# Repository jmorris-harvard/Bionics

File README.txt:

NanoDesign x Bionics Collab File Storage

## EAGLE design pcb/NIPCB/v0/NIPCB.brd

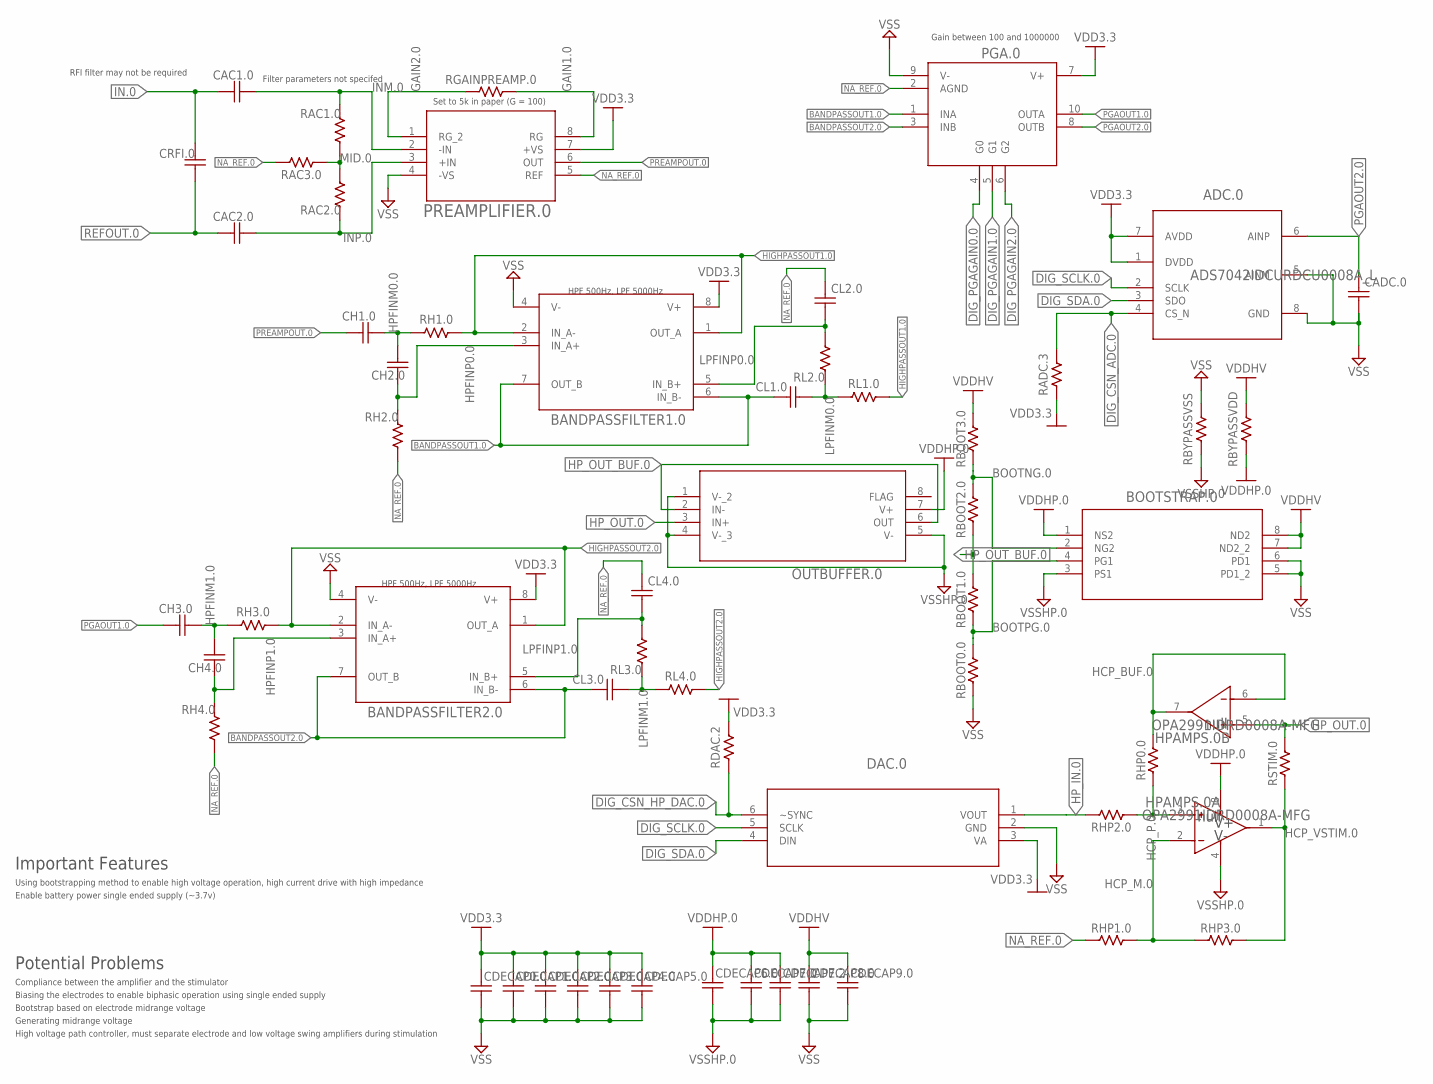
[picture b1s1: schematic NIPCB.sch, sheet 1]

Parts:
ADC.0: ADS7042IDCURDCU0008A_L; DCU0008A_L
BANDPASSFILTER1.0, BANDPASSFILTER2.0: OPA2325IDRD8_TEX; D8_TEX
BOOTSTRAP.0: DMC4047LSD-13SO8_DIO; SO8_DIO
CAC1.0, CAC2.0: C-US0402; 0402
CADC.0: C-US0402; 0402
CDECAP0.0, CDECAP1.0, CDECAP2.0, CDECAP3.0, CDECAP4.0, CDECAP5.0, CDECAP6.0, CDECAP7.0, CDECAP7.2, CDECAP8.0, CDECAP9.0: C-US0402; 0402
CH1.0, CH2.0, CH3.0, CH4.0: C-US0402; 0402
CL1.0, CL2.0, CL3.0, CL4.0: C-US0402; 0402
CRFI.0: C-US0402; 0402
DAC.0: DAC081S101CIMKX/NOPBMK06A; MK06A
HPAMPS.0: OPA2991IDRD0008A-MFG; D0008A-MFG
OUTBUFFER.0: OPA552UA/2K5D8; D8
PGA.0: LTC6911CMS-1TRPBFMSOP-10_MS_LIT; MSOP-10_MS_LIT
PREAMPLIFIER.0: INA818IDSOIC-8_TEX; SOIC-8_TEX
RAC1.0, RAC2.0, RAC3.0: R-US0402; 0402
RADC.3: R-US0402; 0402
RBOOT0.0, RBOOT1.0, RBOOT2.0, RBOOT3.0: R-US0603; 0603
RBYPASSVDD: R-US0402; 0402
RBYPASSVSS: R-US0402; 0402
RDAC.2: R-US0402; 0402
RGAINPREAMP.0: R-US0402; 0402
RH1.0, RH2.0, RH3.0, RH4.0: R-US0402; 0402
RHP0.0, RHP1.0, RHP2.0, RHP3.0: R-US0603; 0603
RL1.0, RL2.0, RL3.0, RL4.0: R-US0402; 0402
RSTIM.0: R-US0603; 0603

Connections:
BANDPASSOUT1.0: BANDPASSFILTER1.0.6 (IN_B-), BANDPASSFILTER1.0.7 (OUT_B), CL1.0.1, PGA.0.1 (INA)
BANDPASSOUT2.0: BANDPASSFILTER2.0.6 (IN_B-), BANDPASSFILTER2.0.7 (OUT_B), CL3.0.1, PGA.0.3 (INB)
BOOTNG.0: BOOTSTRAP.0.2 (NG2), RBOOT2.0.2, RBOOT3.0.1
BOOTPG.0: BOOTSTRAP.0.4 (PG1), RBOOT0.0.2, RBOOT1.0.1
DIG_CSN_ADC.0: ADC.0.4 (CS_N), RADC.3.1; also elsewhere on the board
DIG_CSN_HP_DAC.0: DAC.0.6 (~SYNC), RDAC.2.2; also elsewhere on the board
DIG_PGAGAIN0.0: PGA.0.4 (G0); also elsewhere on the board
DIG_PGAGAIN1.0: PGA.0.5 (G1); also elsewhere on the board
DIG_PGAGAIN2.0: PGA.0.6 (G2); also elsewhere on the board
DIG_SCLK.0: ADC.0.2 (SCLK), DAC.0.5 (SCLK); also elsewhere on the board
DIG_SDA.0: ADC.0.3 (SDO), DAC.0.4 (DIN); also elsewhere on the board
GAIN1.0: PREAMPLIFIER.0.8 (RG), RGAINPREAMP.0.1
GAIN2.0: PREAMPLIFIER.0.1 (RG_2), RGAINPREAMP.0.2
HCP_BUF.0: HPAMPS.0.6 (IN2-), HPAMPS.0.7 (OUT2), RHP0.0.2
HCP_M.0: HPAMPS.0.2 (IN1-), RHP1.0.2, RHP3.0.1
HCP_P.0: HPAMPS.0.3 (IN1+), RHP0.0.1, RHP2.0.1
HCP_VSTIM.0: HPAMPS.0.1 (OUT1), RHP3.0.2, RSTIM.0.1
HIGHPASSOUT1.0: BANDPASSFILTER1.0.1 (OUT_A), BANDPASSFILTER1.0.2 (IN_A-), RH1.0.1, RL1.0.1
HIGHPASSOUT2.0: BANDPASSFILTER2.0.1 (OUT_A), BANDPASSFILTER2.0.2 (IN_A-), RH3.0.1, RL4.0.1
HPFINM0.0: CH1.0.2, CH2.0.2, RH1.0.2
HPFINM1.0: CH3.0.2, CH4.0.2, RH3.0.2
HPFINP0.0: BANDPASSFILTER1.0.3 (IN_A+), CH2.0.1, RH2.0.1
HPFINP1.0: BANDPASSFILTER2.0.3 (IN_A+), CH4.0.1, RH4.0.1
HP_IN.0: DAC.0.1 (VOUT), RHP2.0.2
HP_OUT.0: HPAMPS.0.5 (IN2+), OUTBUFFER.0.3 (IN+), RSTIM.0.2; also elsewhere on the board
HP_OUT_BUF.0: OUTBUFFER.0.2 (IN-), OUTBUFFER.0.6 (OUT), RBOOT1.0.2, RBOOT2.0.1
IN.0: CAC1.0.1, CRFI.0.2; also elsewhere on the board
INM.0: CAC1.0.2, PREAMPLIFIER.0.2 (-IN), RAC1.0.2
INP.0: CAC2.0.2, PREAMPLIFIER.0.3 (+IN), RAC2.0.1
LPFINM0.0: CL1.0.2, RL1.0.2, RL2.0.1
LPFINM1.0: CL3.0.2, RL3.0.1, RL4.0.2
LPFINP0.0: BANDPASSFILTER1.0.5 (IN_B+), CL2.0.1, RL2.0.2
LPFINP1.0: BANDPASSFILTER2.0.5 (IN_B+), CL4.0.1, RL3.0.2
MID.0: RAC1.0.1, RAC2.0.2, RAC3.0.1
NA_REF.0: CL2.0.2, CL4.0.2, PGA.0.2 (AGND), PREAMPLIFIER.0.5 (REF), RAC3.0.2, RH2.0.2, RH4.0.2, RHP1.0.1; also elsewhere on the board
PGAOUT1.0: CH3.0.1, PGA.0.10 (OUTA)
PGAOUT2.0: ADC.0.6 (AINP), CADC.0.2, PGA.0.8 (OUTB)
PREAMPOUT.0: CH1.0.1, PREAMPLIFIER.0.6 (OUT)
REFOUT.0: CAC2.0.1, CRFI.0.1; also elsewhere on the board
VDD3.3: ADC.0.1 (DVDD), ADC.0.7 (AVDD), BANDPASSFILTER1.0.8 (V+), BANDPASSFILTER2.0.8 (V+), CDECAP0.0.1, CDECAP1.0.1, CDECAP2.0.1, CDECAP3.0.1, CDECAP4.0.1, CDECAP5.0.1, DAC.0.3 (VA), PGA.0.7 (V+), PREAMPLIFIER.0.7 (+VS), RADC.3.2, RDAC.2.1; also elsewhere on the board
VDDHP.0: BOOTSTRAP.0.1 (NS2), CDECAP6.0.1, CDECAP7.0.1, CDECAP7.2.1, HPAMPS.0.8 (V+), OUTBUFFER.0.7 (V+), RBYPASSVDD.2
VDDHV: BOOTSTRAP.0.7 (ND2_2), BOOTSTRAP.0.8 (ND2), CDECAP8.0.1, CDECAP9.0.1, RBOOT3.0.2, RBYPASSVDD.1; also elsewhere on the board
VSS: ADC.0.5 (AINM), ADC.0.8 (GND), BANDPASSFILTER1.0.4 (V-), BANDPASSFILTER2.0.4 (V-), BOOTSTRAP.0.5 (PD1_2), BOOTSTRAP.0.6 (PD1), CADC.0.1, CDECAP0.0.2, CDECAP1.0.2, CDECAP2.0.2, CDECAP3.0.2, CDECAP4.0.2, CDECAP5.0.2, CDECAP8.0.2, CDECAP9.0.2, DAC.0.2 (GND), PGA.0.9 (V-), PREAMPLIFIER.0.4 (-VS), RBOOT0.0.1, RBYPASSVSS.1; also elsewhere on the board
VSSHP.0: BOOTSTRAP.0.3 (PS1), CDECAP6.0.2, CDECAP7.0.2, CDECAP7.2.2, HPAMPS.0.4 (V-), OUTBUFFER.0.1 (V-_2), OUTBUFFER.0.4 (V-_3), OUTBUFFER.0.5 (V-), RBYPASSVSS.2

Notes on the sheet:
Set to 5k in paper (G = 100)
Filter parameters not specifed
RFI filter may not be required
HPF 500Hz, LPF 5000Hz
Gain between 100 and 1000000
Potential Problems
Compliance between the amplifier and the stimulator
Biasing the electrodes to enable biphasic operation using single ended supply
Important Features
Using bootstrapping method to enable high voltage operation, high current drive with high impedance
Enable battery power single ended supply (~3.7v)
Bootstrap based on electrode midrange voltage
Generating midrange voltage
High voltage path controller, must separate electrode and low voltage swing amplifiers during stimulation

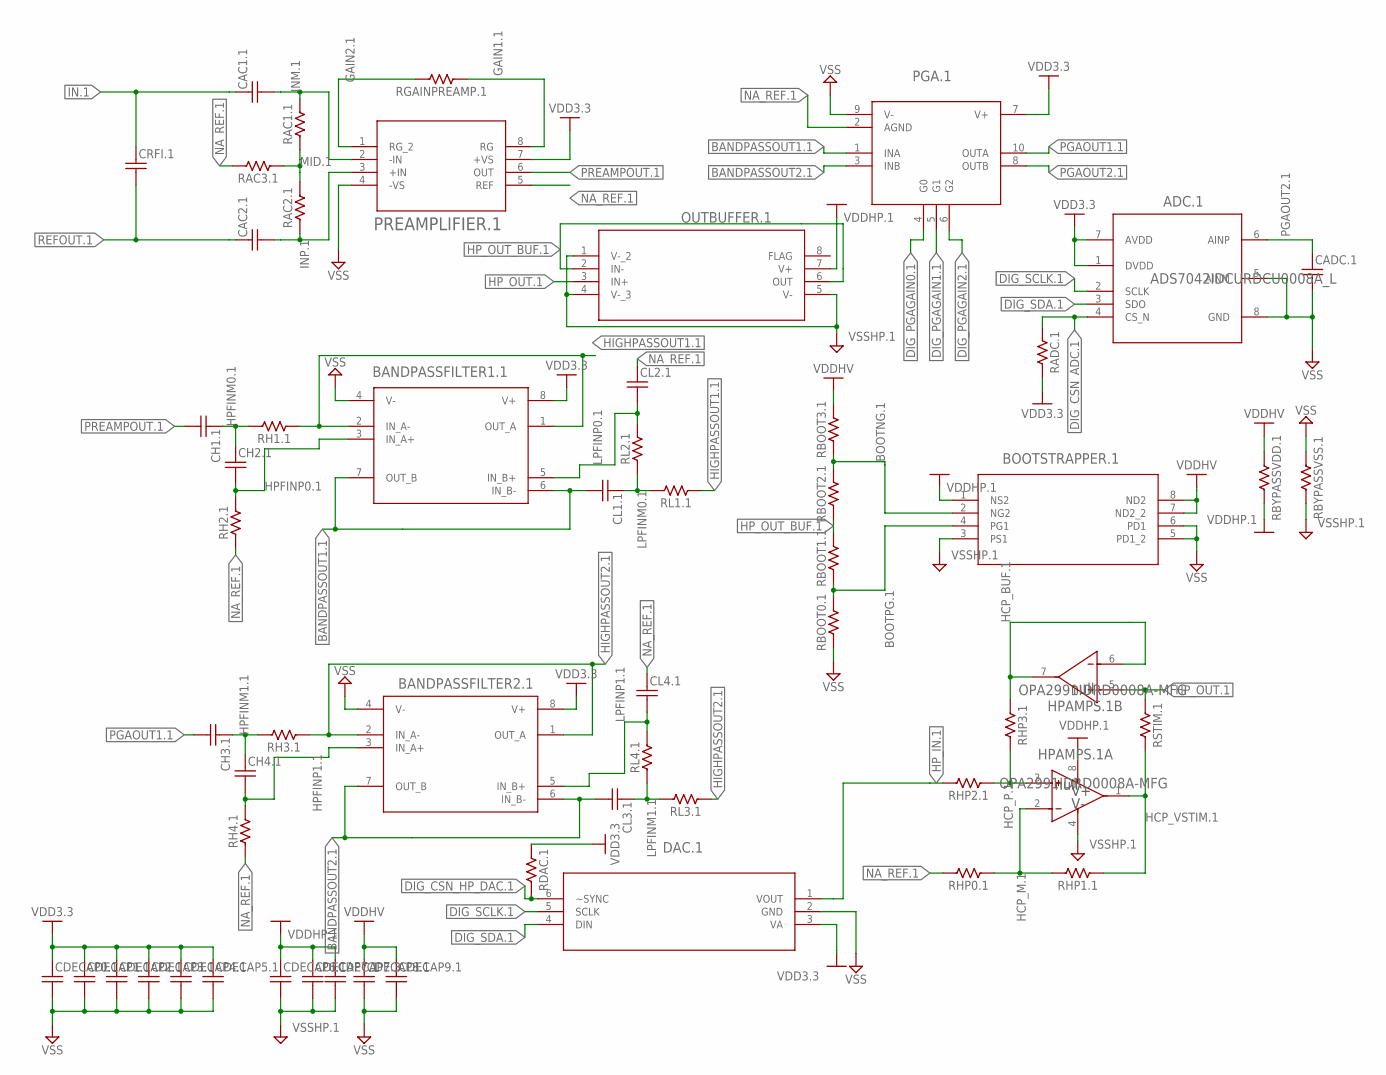
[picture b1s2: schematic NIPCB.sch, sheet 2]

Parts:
ADC.1: ADS7042IDCURDCU0008A_L; DCU0008A_L
BANDPASSFILTER1.1, BANDPASSFILTER2.1: OPA2325IDRD8_TEX-L; D8_TEX-L
BOOTSTRAPPER.1: DMC4047LSD-13SO8_DIO; SO8_DIO
CAC1.1, CAC2.1: C-US0402; 0402
CADC.1: C-US0402; 0402
CDECAP0.1, CDECAP1.1, CDECAP2.1, CDECAP3.1, CDECAP4.1, CDECAP5.1, CDECAP6.1, CDECAP7.1, CDECAP7.3, CDECAP8.1, CDECAP9.1: C-US0402; 0402
CH1.1, CH2.1, CH3.1, CH4.1: C-US0402; 0402
CL1.1, CL2.1, CL3.1, CL4.1: C-US0402; 0402
CRFI.1: C-US0402; 0402
DAC.1: DAC081S101CIMKX/NOPBMK06A; MK06A
HPAMPS.1: OPA2991IDRD0008A-MFG; D0008A-MFG
OUTBUFFER.1: OPA552UA/2K5D8; D8
PGA.1: LTC6911CMS-1TRPBFMSOP-10_MS_LIT; MSOP-10_MS_LIT
PREAMPLIFIER.1: INA818IDSOIC-8_TEX; SOIC-8_TEX
RAC1.1, RAC2.1, RAC3.1: R-US0402; 0402
RADC.1: R-US0402; 0402
RBOOT0.1, RBOOT1.1, RBOOT2.1, RBOOT3.1: R-US0603; 0603
RBYPASSVDD.1: R-US0402; 0402
RBYPASSVSS.1: R-US0402; 0402
RDAC.1: R-US0402; 0402
RGAINPREAMP.1: R-US0402; 0402
RH1.1, RH2.1, RH3.1, RH4.1: R-US0402; 0402
RHP0.1, RHP1.1, RHP2.1, RHP3.1: R-US0603; 0603
RL1.1, RL2.1, RL3.1, RL4.1: R-US0402; 0402
RSTIM.1: R-US0603; 0603

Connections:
BANDPASSOUT1.1: BANDPASSFILTER1.1.6 (IN_B-), BANDPASSFILTER1.1.7 (OUT_B), CL1.1.2, PGA.1.1 (INA)
BANDPASSOUT2.1: BANDPASSFILTER2.1.6 (IN_B-), BANDPASSFILTER2.1.7 (OUT_B), CL3.1.2, PGA.1.3 (INB)
BOOTNG.1: BOOTSTRAPPER.1.2 (NG2), RBOOT2.1.2, RBOOT3.1.1
BOOTPG.1: BOOTSTRAPPER.1.4 (PG1), RBOOT0.1.2, RBOOT1.1.1
DIG_CSN_ADC.1: ADC.1.4 (CS_N), RADC.1.1; also elsewhere on the board
DIG_CSN_HP_DAC.1: DAC.1.6 (~SYNC), RDAC.1.2; also elsewhere on the board
DIG_PGAGAIN0.1: PGA.1.4 (G0); also elsewhere on the board
DIG_PGAGAIN1.1: PGA.1.5 (G1); also elsewhere on the board
DIG_PGAGAIN2.1: PGA.1.6 (G2); also elsewhere on the board
DIG_SCLK.1: ADC.1.2 (SCLK), DAC.1.5 (SCLK); also elsewhere on the board
DIG_SDA.1: ADC.1.3 (SDO), DAC.1.4 (DIN); also elsewhere on the board
GAIN1.1: PREAMPLIFIER.1.8 (RG), RGAINPREAMP.1.1
GAIN2.1: PREAMPLIFIER.1.1 (RG_2), RGAINPREAMP.1.2
HCP_BUF.1: HPAMPS.1.6 (IN2-), HPAMPS.1.7 (OUT2), RHP3.1.1
HCP_M.1: HPAMPS.1.2 (IN1-), RHP0.1.1, RHP1.1.2
HCP_P.1: HPAMPS.1.3 (IN1+), RHP2.1.1, RHP3.1.2
HCP_VSTIM.1: HPAMPS.1.1 (OUT1), RHP1.1.1, RSTIM.1.2
HIGHPASSOUT1.1: BANDPASSFILTER1.1.1 (OUT_A), BANDPASSFILTER1.1.2 (IN_A-), RH1.1.1, RL1.1.1
HIGHPASSOUT2.1: BANDPASSFILTER2.1.1 (OUT_A), BANDPASSFILTER2.1.2 (IN_A-), RH3.1.1, RL3.1.1
HPFINM0.1: CH1.1.1, CH2.1.1, RH1.1.2
HPFINM1.1: CH3.1.1, CH4.1.1, RH3.1.2
HPFINP0.1: BANDPASSFILTER1.1.3 (IN_A+), CH2.1.2, RH2.1.2
HPFINP1.1: BANDPASSFILTER2.1.3 (IN_A+), CH4.1.2, RH4.1.2
HP_IN.1: DAC.1.1 (VOUT), RHP2.1.2
HP_OUT.1: HPAMPS.1.5 (IN2+), OUTBUFFER.1.3 (IN+), RSTIM.1.1; also elsewhere on the board
HP_OUT_BUF.1: OUTBUFFER.1.2 (IN-), OUTBUFFER.1.6 (OUT), RBOOT1.1.2, RBOOT2.1.1
IN.1: CAC1.1.1, CRFI.1.1; also elsewhere on the board
INM.1: CAC1.1.2, PREAMPLIFIER.1.2 (-IN), RAC1.1.2
INP.1: CAC2.1.2, PREAMPLIFIER.1.3 (+IN), RAC2.1.1
LPFINM0.1: CL1.1.1, RL1.1.2, RL2.1.1
LPFINM1.1: CL3.1.1, RL3.1.2, RL4.1.1
LPFINP0.1: BANDPASSFILTER1.1.5 (IN_B+), CL2.1.2, RL2.1.2
LPFINP1.1: BANDPASSFILTER2.1.5 (IN_B+), CL4.1.2, RL4.1.2
MID.1: RAC1.1.1, RAC2.1.2, RAC3.1.1
NA_REF.1: CL2.1.1, CL4.1.1, PGA.1.2 (AGND), PREAMPLIFIER.1.5 (REF), RAC3.1.2, RH2.1.1, RH4.1.1, RHP0.1.2; also elsewhere on the board
PGAOUT1.1: CH3.1.2, PGA.1.10 (OUTA)
PGAOUT2.1: ADC.1.6 (AINP), CADC.1.1, PGA.1.8 (OUTB)
PREAMPOUT.1: CH1.1.2, PREAMPLIFIER.1.6 (OUT)
REFOUT.1: CAC2.1.1, CRFI.1.2; also elsewhere on the board
VDD3.3: ADC.1.1 (DVDD), ADC.1.7 (AVDD), BANDPASSFILTER1.1.8 (V+), BANDPASSFILTER2.1.8 (V+), CDECAP0.1.1, CDECAP1.1.1, CDECAP2.1.1, CDECAP3.1.1, CDECAP4.1.1, CDECAP5.1.1, DAC.1.3 (VA), PGA.1.7 (V+), PREAMPLIFIER.1.7 (+VS), RADC.1.2, RDAC.1.1; also elsewhere on the board
VDDHP.1: BOOTSTRAPPER.1.1 (NS2), CDECAP6.1.1, CDECAP7.1.1, CDECAP7.3.1, HPAMPS.1.8 (V+), OUTBUFFER.1.7 (V+), RBYPASSVDD.1.2
VDDHV: BOOTSTRAPPER.1.7 (ND2_2), BOOTSTRAPPER.1.8 (ND2), CDECAP8.1.1, CDECAP9.1.1, RBOOT3.1.2, RBYPASSVDD.1.1; also elsewhere on the board
VSS: ADC.1.5 (AINM), ADC.1.8 (GND), BANDPASSFILTER1.1.4 (V-), BANDPASSFILTER2.1.4 (V-), BOOTSTRAPPER.1.5 (PD1_2), BOOTSTRAPPER.1.6 (PD1), CADC.1.2, CDECAP0.1.2, CDECAP1.1.2, CDECAP2.1.2, CDECAP3.1.2, CDECAP4.1.2, CDECAP5.1.2, CDECAP8.1.2, CDECAP9.1.2, DAC.1.2 (GND), PGA.1.9 (V-), PREAMPLIFIER.1.4 (-VS), RBOOT0.1.1, RBYPASSVSS.1.1; also elsewhere on the board
VSSHP.1: BOOTSTRAPPER.1.3 (PS1), CDECAP6.1.2, CDECAP7.1.2, CDECAP7.3.2, HPAMPS.1.4 (V-), OUTBUFFER.1.1 (V-_2), OUTBUFFER.1.4 (V-_3), OUTBUFFER.1.5 (V-), RBYPASSVSS.1.2

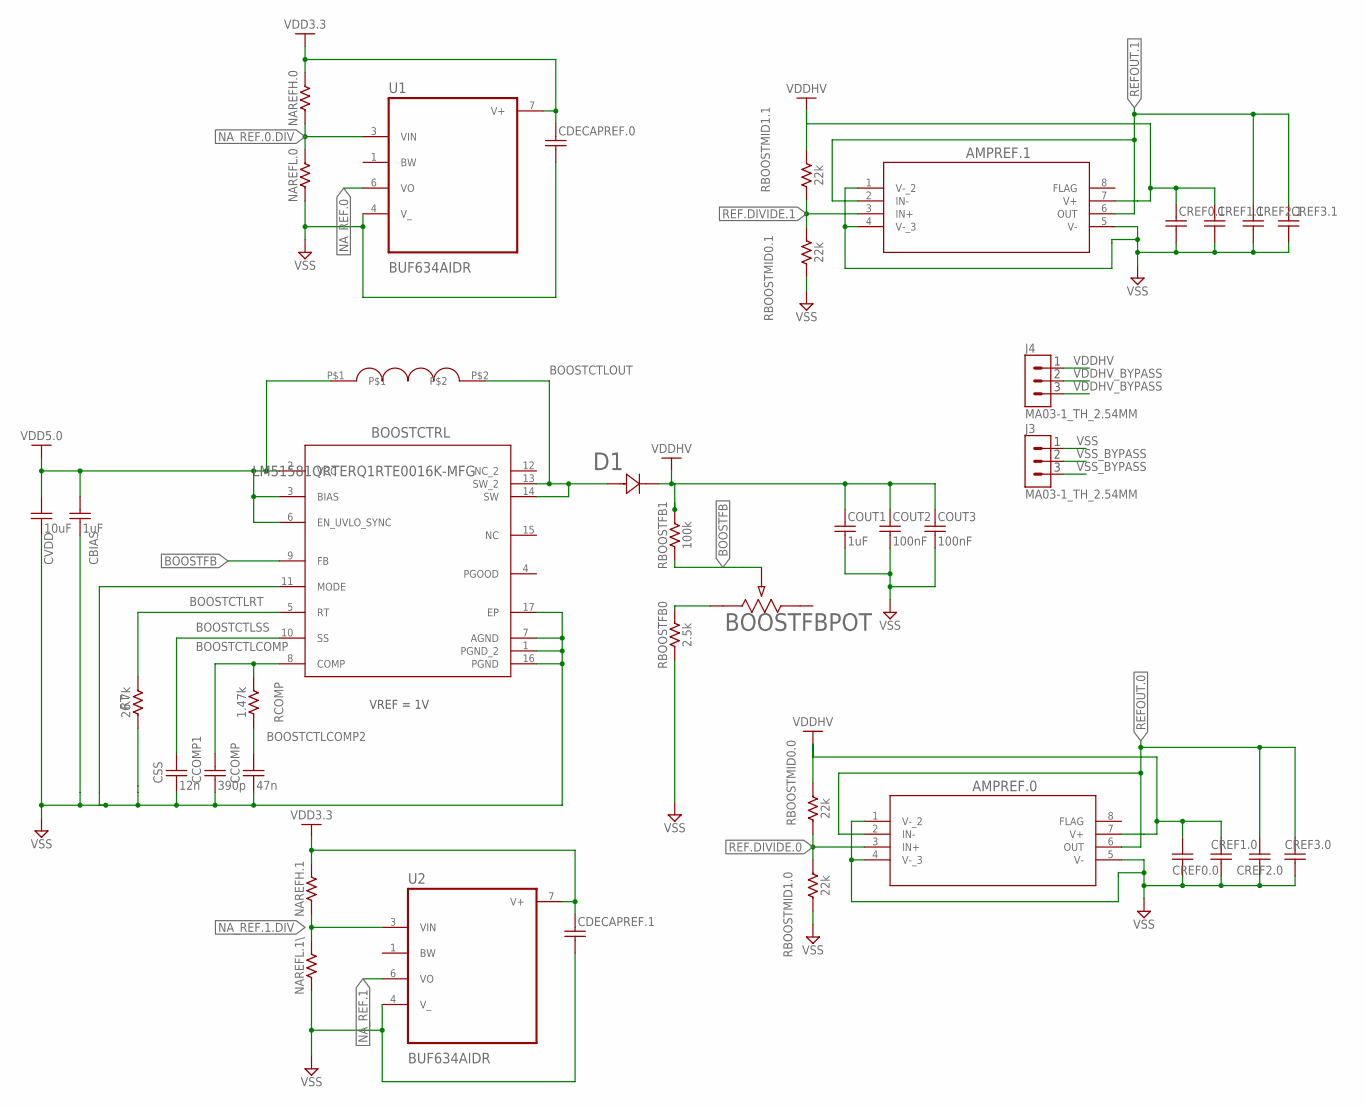
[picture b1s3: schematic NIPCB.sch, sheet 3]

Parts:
AMPREF.0, AMPREF.1: OPA552UA/2K5D8; D8
BOOSTCTRL: LM51581QRTERQ1RTE0016K-MFG; RTE0016K-MFG
BOOSTFBPOT: 3362P-1-103LFPOT_3362P; POT_3362P
CBIAS: 1uF; 0805
CCOMP: 47n; 0603
CCOMP1: 390p; 0603
CDECAPREF.0, CDECAPREF.1: C-US0402; 0402
COUT1: 1uF; 0805
COUT2, COUT3: 100nF; 0805
CREF0.0, CREF0.1, CREF2.0, CREF2.1: C-US0603; 0603
CREF1.0, CREF1.1, CREF3.0, CREF3.1: C-US0805; 0805
CSS: 12n; 0603
CVDD: 10uF; 0805
D1: B160-13-FSMA_DIO; SMA_DIO
J3, J4: MA03-1_TH_2.54MM
NAREFH.0, NAREFH.1: R-US0402; 0402
NAREFL.0, NAREFL.1\: R-US0402; 0402
RBOOSTFB0: 2.5k; 0603
RBOOSTFB1: 100k; 0603
RBOOSTMID0.0, RBOOSTMID0.1, RBOOSTMID1.0, RBOOSTMID1.1: 22k; 0603
RCOMP: 1.47k; 0603
RT: 26.7k; 0603
U1, U2: BUF634AIDR; SOIC127P599X175-8N
U$1: MSS1246-COILCRAFT

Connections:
BOOSTCTLCOMP: BOOSTCTRL.8 (COMP), CCOMP1.1, RCOMP.1
BOOSTCTLCOMP2: CCOMP.1, RCOMP.2
BOOSTCTLOUT: BOOSTCTRL.13 (SW_2), BOOSTCTRL.14 (SW), D1.2, U$1.P$2
BOOSTCTLRT: BOOSTCTRL.5 (RT), RT.1
BOOSTCTLSS: BOOSTCTRL.10 (SS), CSS.1
BOOSTFB: BOOSTCTRL.9 (FB), BOOSTFBPOT.2, RBOOSTFB1.1
unnamed: BOOSTFBPOT.1, RBOOSTFB0.2
NA_REF.0: U1.6 (VO); also elsewhere on the board
NA_REF.0.DIV: NAREFH.0.1, NAREFL.0.2, U1.3 (VIN)
NA_REF.1: U2.6 (VO); also elsewhere on the board
NA_REF.1.DIV: NAREFH.1.1, NAREFL.1\.2, U2.3 (VIN)
REF.DIVIDE.0: AMPREF.0.3 (IN+), RBOOSTMID0.0.1, RBOOSTMID1.0.2
REF.DIVIDE.1: AMPREF.1.3 (IN+), RBOOSTMID0.1.2, RBOOSTMID1.1.1
REFOUT.0: AMPREF.0.2 (IN-), AMPREF.0.6 (OUT), CREF2.0.1, CREF3.0.1; also elsewhere on the board
REFOUT.1: AMPREF.1.2 (IN-), AMPREF.1.6 (OUT), CREF2.1.1, CREF3.1.1; also elsewhere on the board
VDD3.3: CDECAPREF.0.1, CDECAPREF.1.1, NAREFH.0.2, NAREFH.1.2, U1.7 (V+), U2.7 (V+); also elsewhere on the board
VDD5.0: BOOSTCTRL.2 (VCC), BOOSTCTRL.3 (BIAS), BOOSTCTRL.6 (EN_UVLO_SYNC), CBIAS.1, CVDD.1, U$1.P$1; also elsewhere on the board
VDDHV: AMPREF.0.7 (V+), AMPREF.1.7 (V+), COUT1.1, COUT2.1, COUT3.1, CREF0.0.1, CREF0.1.1, CREF1.0.1, CREF1.1.1, D1.1, J4.1, RBOOSTFB1.2, RBOOSTMID0.0.2, RBOOSTMID1.1.2; also elsewhere on the board
VDDHV_BYPASS: J4.2, J4.3
VSS: AMPREF.0.1 (V-_2), AMPREF.0.4 (V-_3), AMPREF.0.5 (V-), AMPREF.1.1 (V-_2), AMPREF.1.4 (V-_3), AMPREF.1.5 (V-), BOOSTCTRL.1 (PGND_2), BOOSTCTRL.7 (AGND), BOOSTCTRL.11 (MODE), BOOSTCTRL.16 (PGND), BOOSTCTRL.17 (EP), CBIAS.2, CCOMP.2, CCOMP1.2, CDECAPREF.0.2, CDECAPREF.1.2, COUT1.2, COUT2.2, COUT3.2, CREF0.0.2, CREF0.1.2, CREF1.0.2, CREF1.1.2, CREF2.0.2, CREF2.1.2, CREF3.0.2, CREF3.1.2, CSS.2, CVDD.2, J3.1, NAREFL.0.1, NAREFL.1\.1, RBOOSTFB0.1, RBOOSTMID0.1.1, RBOOSTMID1.0.1, RT.2, U1.4 (V_), U2.4 (V_); also elsewhere on the board
VSS_BYPASS: J3.2, J3.3

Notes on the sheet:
VREF = 1V

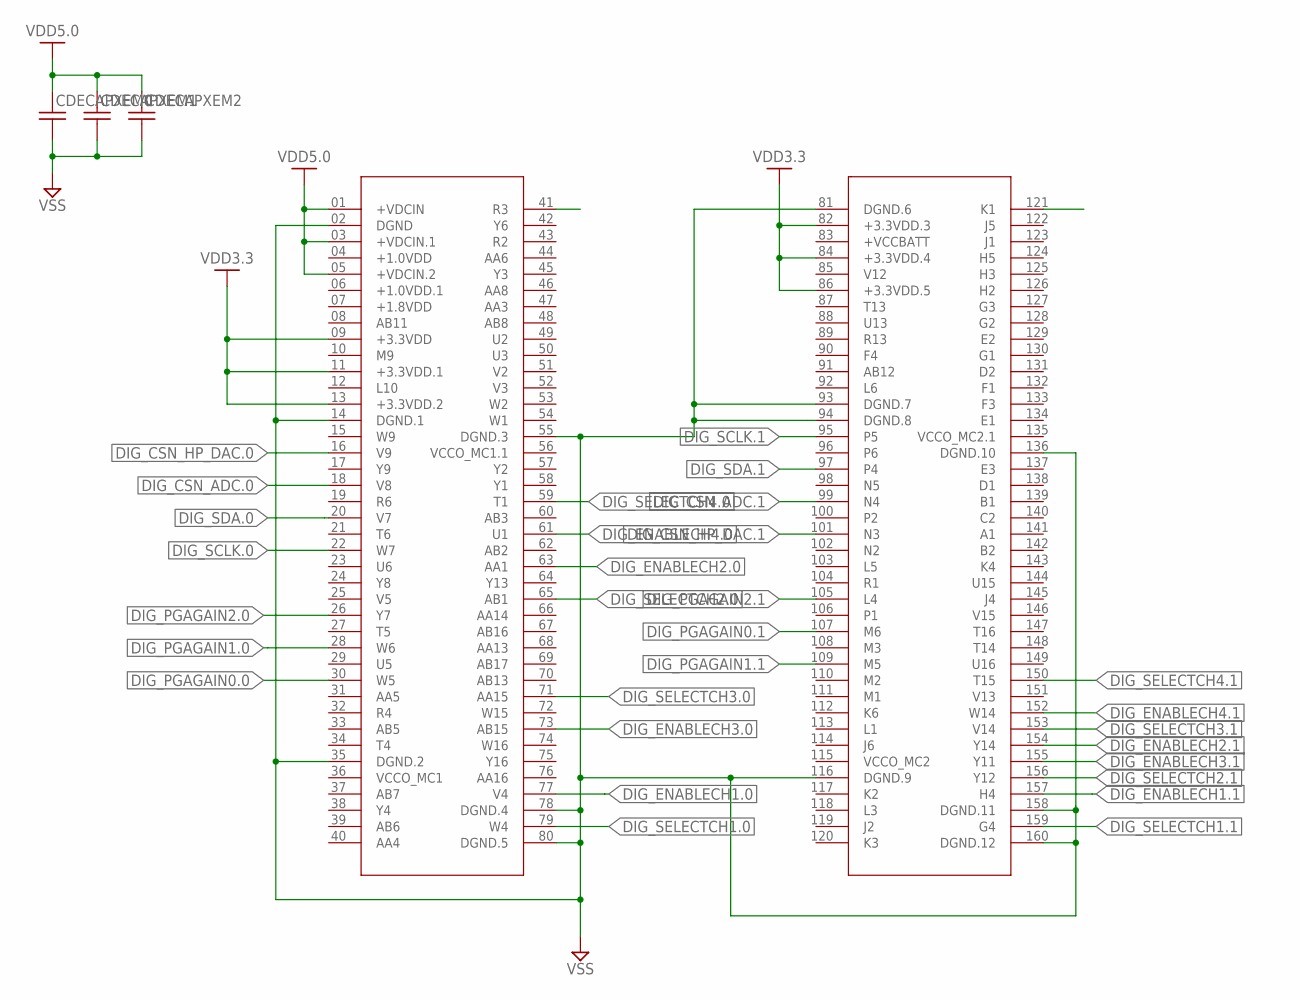
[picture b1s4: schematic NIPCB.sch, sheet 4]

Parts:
CDECAPXEM0: C-US0805; 0805
CDECAPXEM1, CDECAPXEM2: C-US0603; 0603
U$2: XEM7310

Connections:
DIG_CSN_ADC.0: U$2.18 (V8); also elsewhere on the board
DIG_CSN_ADC.1: U$2.99 (N4); also elsewhere on the board
DIG_CSN_HP_DAC.0: U$2.16 (V9); also elsewhere on the board
DIG_CSN_HP_DAC.1: U$2.101 (N3); also elsewhere on the board
DIG_ENABLECH1.0: U$2.77 (V4); also elsewhere on the board
DIG_ENABLECH1.1: U$2.157 (H4); also elsewhere on the board
DIG_ENABLECH2.0: U$2.63 (AA1); also elsewhere on the board
DIG_ENABLECH2.1: U$2.154 (Y14); also elsewhere on the board
DIG_ENABLECH3.0: U$2.73 (AB15); also elsewhere on the board
DIG_ENABLECH3.1: U$2.155 (Y11); also elsewhere on the board
DIG_ENABLECH4.0: U$2.61 (U1); also elsewhere on the board
DIG_ENABLECH4.1: U$2.152 (W14); also elsewhere on the board
DIG_PGAGAIN0.0: U$2.30 (W5); also elsewhere on the board
DIG_PGAGAIN0.1: U$2.107 (M6); also elsewhere on the board
DIG_PGAGAIN1.0: U$2.28 (W6); also elsewhere on the board
DIG_PGAGAIN1.1: U$2.109 (M5); also elsewhere on the board
DIG_PGAGAIN2.0: U$2.26 (Y7); also elsewhere on the board
DIG_PGAGAIN2.1: U$2.105 (L4); also elsewhere on the board
DIG_SCLK.0: U$2.22 (W7); also elsewhere on the board
DIG_SCLK.1: U$2.95 (P5); also elsewhere on the board
DIG_SDA.0: U$2.20 (V7); also elsewhere on the board
DIG_SDA.1: U$2.97 (P4); also elsewhere on the board
DIG_SELECTCH1.0: U$2.79 (W4); also elsewhere on the board
DIG_SELECTCH1.1: U$2.159 (G4); also elsewhere on the board
DIG_SELECTCH2.0: U$2.65 (AB1); also elsewhere on the board
DIG_SELECTCH2.1: U$2.156 (Y12); also elsewhere on the board
DIG_SELECTCH3.0: U$2.71 (AA15); also elsewhere on the board
DIG_SELECTCH3.1: U$2.153 (V14); also elsewhere on the board
DIG_SELECTCH4.0: U$2.59 (T1); also elsewhere on the board
DIG_SELECTCH4.1: U$2.150 (T15); also elsewhere on the board
VDD3.3: U$2.09 (+3.3VDD), U$2.11 (+3.3VDD.1), U$2.13 (+3.3VDD.2), U$2.82 (+3.3VDD.3), U$2.84 (+3.3VDD.4), U$2.86 (+3.3VDD.5); also elsewhere on the board
VDD5.0: CDECAPXEM0.1, CDECAPXEM1.1, CDECAPXEM2.1, U$2.01 (+VDCIN), U$2.03 (+VDCIN.1), U$2.05 (+VDCIN.2); also elsewhere on the board
VSS: CDECAPXEM0.2, CDECAPXEM1.2, CDECAPXEM2.2, U$2.02 (DGND), U$2.14 (DGND.1), U$2.35 (DGND.2), U$2.55 (DGND.3), U$2.78 (DGND.4), U$2.80 (DGND.5), U$2.81 (DGND.6), U$2.93 (DGND.7), U$2.94 (DGND.8), U$2.116 (DGND.9), U$2.136 (DGND.10), U$2.158 (DGND.11), U$2.160 (DGND.12); also elsewhere on the board

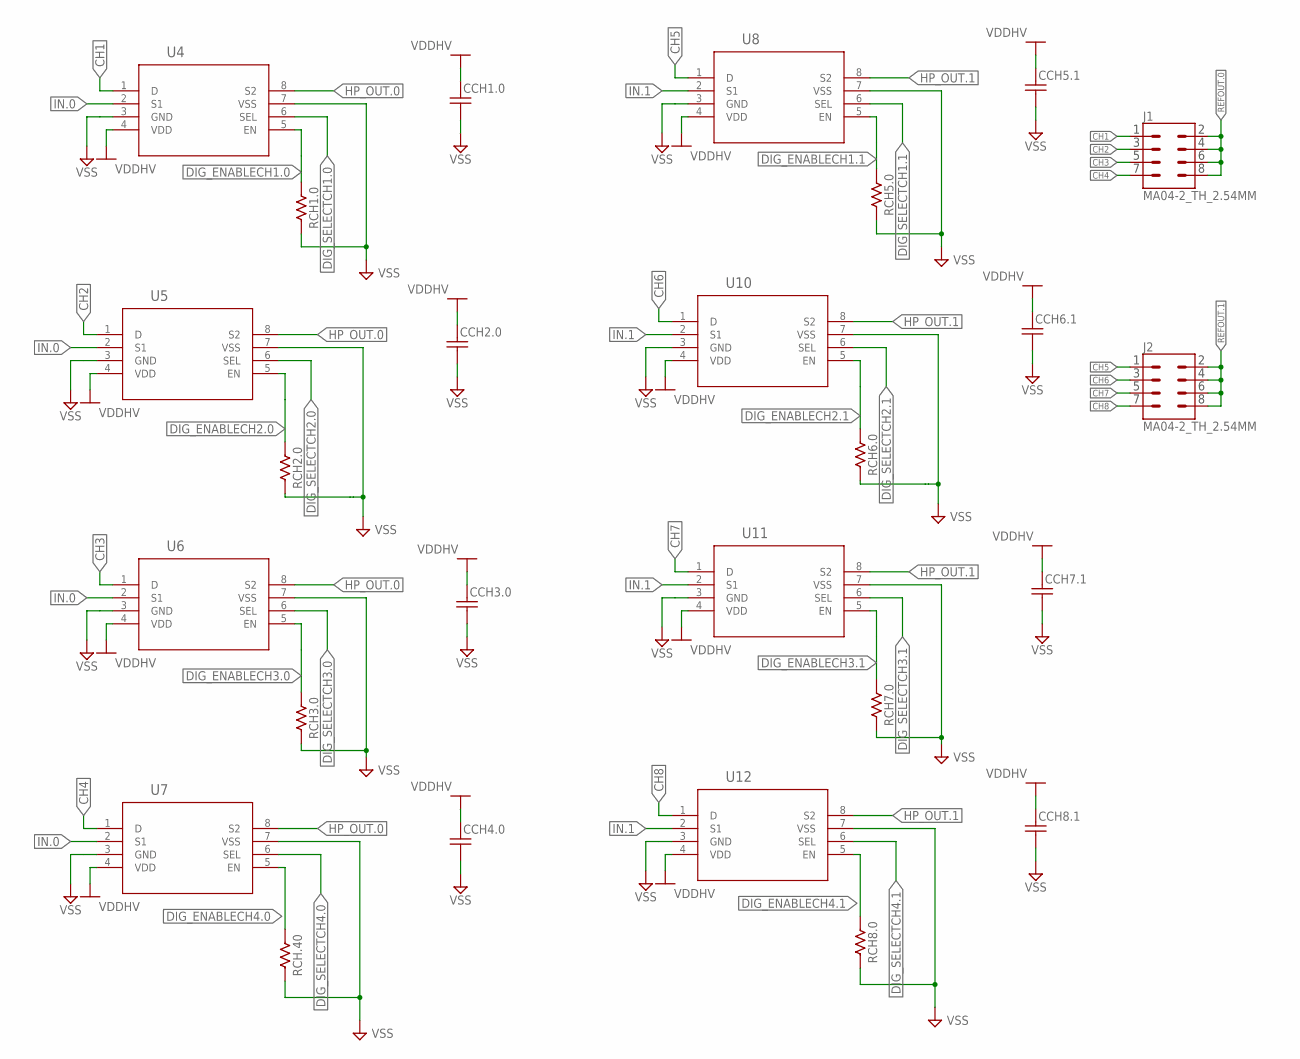
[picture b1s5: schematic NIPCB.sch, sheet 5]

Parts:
CCH1.0, CCH2.0, CCH3.0, CCH4.0, CCH5.1, CCH6.1, CCH7.1, CCH8.1: C-US0402; 0402
J1, J2: MA04-2_TH_2.54MM
RCH1.0, RCH2.0, RCH3.0, RCH5.0, RCH6.0, RCH7.0, RCH8.0, RCH.40: R-US0402; 0402
U4, U5, U6, U7, U8, U10, U11, U12: TMUX7219DGKRVSSOP_9DGKR_TEX; VSSOP_9DGKR_TEX

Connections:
CH1: J1.1, U4.1 (D)
CH2: J1.3, U5.1 (D)
CH3: J1.5, U6.1 (D)
CH4: J1.7, U7.1 (D)
CH5: J2.1, U8.1 (D)
CH6: J2.3, U10.1 (D)
CH7: J2.5, U11.1 (D)
CH8: J2.7, U12.1 (D)
DIG_ENABLECH1.0: RCH1.0.1, U4.5 (EN); also elsewhere on the board
DIG_ENABLECH1.1: RCH5.0.1, U8.5 (EN); also elsewhere on the board
DIG_ENABLECH2.0: RCH2.0.1, U5.5 (EN); also elsewhere on the board
DIG_ENABLECH2.1: RCH6.0.1, U10.5 (EN); also elsewhere on the board
DIG_ENABLECH3.0: RCH3.0.1, U6.5 (EN); also elsewhere on the board
DIG_ENABLECH3.1: RCH7.0.1, U11.5 (EN); also elsewhere on the board
DIG_ENABLECH4.0: RCH.40.1, U7.5 (EN); also elsewhere on the board
DIG_ENABLECH4.1: RCH8.0.1, U12.5 (EN); also elsewhere on the board
DIG_SELECTCH1.0: U4.6 (SEL); also elsewhere on the board
DIG_SELECTCH1.1: U8.6 (SEL); also elsewhere on the board
DIG_SELECTCH2.0: U5.6 (SEL); also elsewhere on the board
DIG_SELECTCH2.1: U10.6 (SEL); also elsewhere on the board
DIG_SELECTCH3.0: U6.6 (SEL); also elsewhere on the board
DIG_SELECTCH3.1: U11.6 (SEL); also elsewhere on the board
DIG_SELECTCH4.0: U7.6 (SEL); also elsewhere on the board
DIG_SELECTCH4.1: U12.6 (SEL); also elsewhere on the board
HP_OUT.0: U4.8 (S2), U5.8 (S2), U6.8 (S2), U7.8 (S2); also elsewhere on the board
HP_OUT.1: U8.8 (S2), U10.8 (S2), U11.8 (S2), U12.8 (S2); also elsewhere on the board
IN.0: U4.2 (S1), U5.2 (S1), U6.2 (S1), U7.2 (S1); also elsewhere on the board
IN.1: U8.2 (S1), U10.2 (S1), U11.2 (S1), U12.2 (S1); also elsewhere on the board
REFOUT.0: J1.2, J1.4, J1.6, J1.8; also elsewhere on the board
REFOUT.1: J2.2, J2.4, J2.6, J2.8; also elsewhere on the board
VDDHV: CCH1.0.1, CCH2.0.1, CCH3.0.1, CCH4.0.1, CCH5.1.1, CCH6.1.1, CCH7.1.1, CCH8.1.1, U4.4 (VDD), U5.4 (VDD), U6.4 (VDD), U7.4 (VDD), U8.4 (VDD), U10.4 (VDD), U11.4 (VDD), U12.4 (VDD); also elsewhere on the board
VSS: CCH1.0.2, CCH2.0.2, CCH3.0.2, CCH4.0.2, CCH5.1.2, CCH6.1.2, CCH7.1.2, CCH8.1.2, RCH1.0.2, RCH2.0.2, RCH3.0.2, RCH5.0.2, RCH6.0.2, RCH7.0.2, RCH8.0.2, RCH.40.2, U4.3 (GND), U4.7 (VSS), U5.3 (GND), U5.7 (VSS), U6.3 (GND), U6.7 (VSS), U7.3 (GND), U7.7 (VSS), U8.3 (GND), U8.7 (VSS), U10.3 (GND), U10.7 (VSS), U11.3 (GND), U11.7 (VSS), U12.3 (GND), U12.7 (VSS); also elsewhere on the board

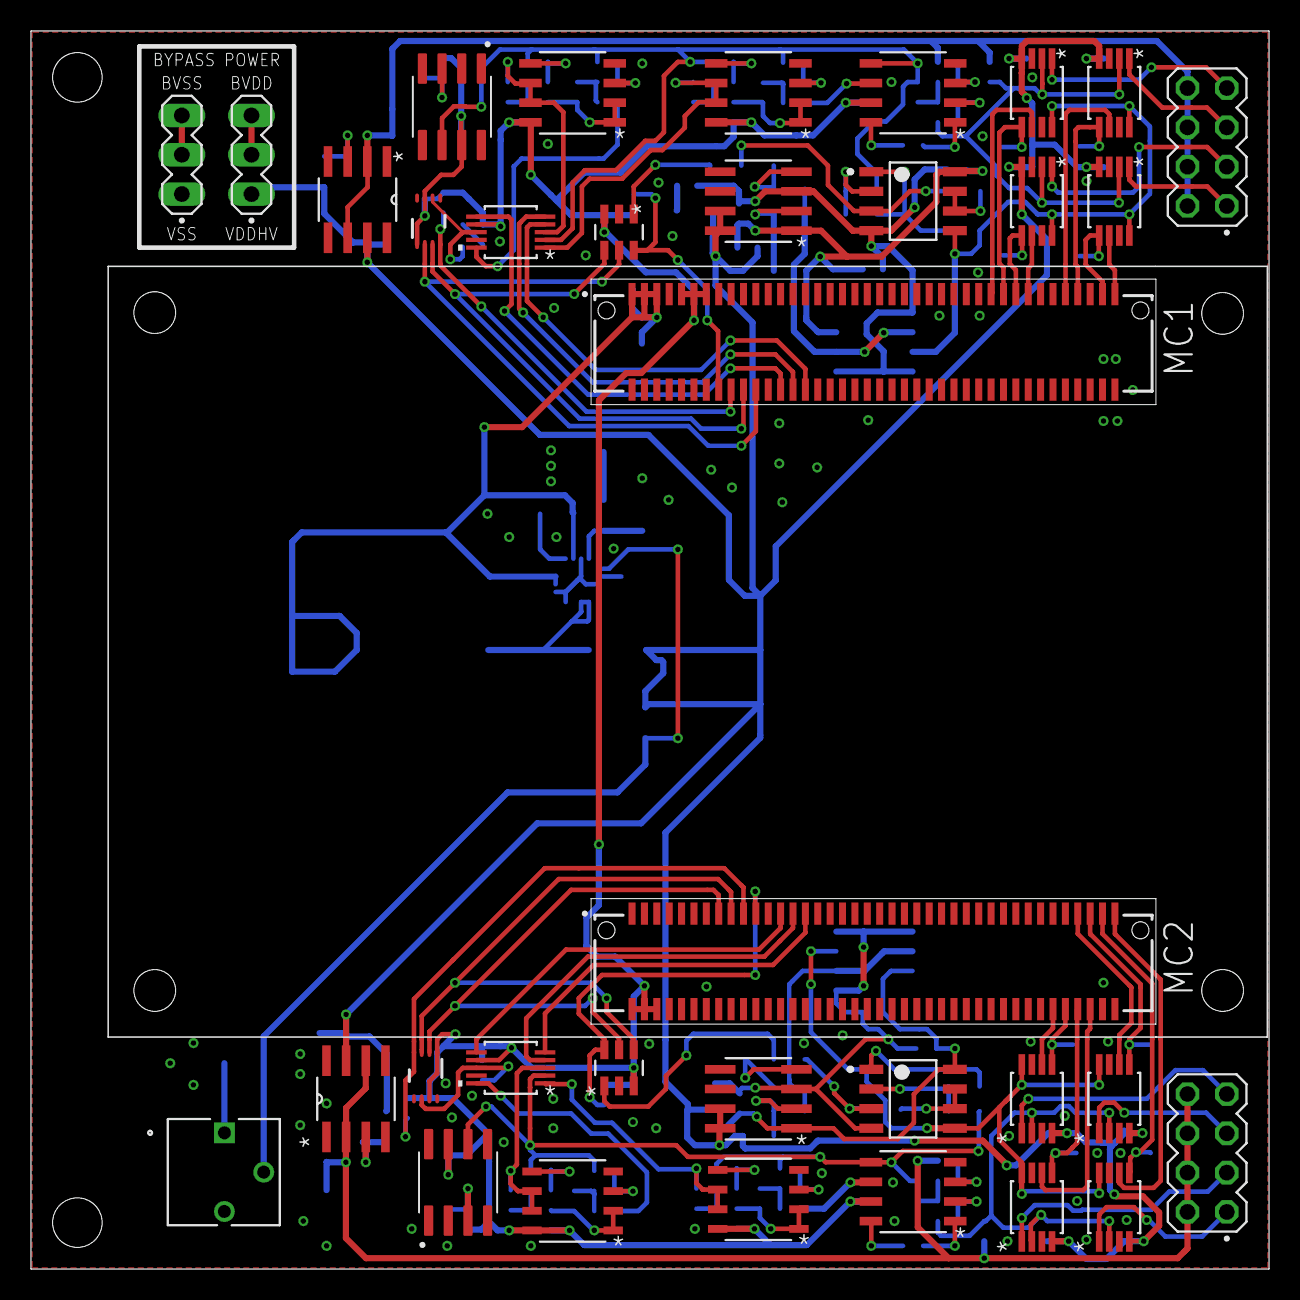
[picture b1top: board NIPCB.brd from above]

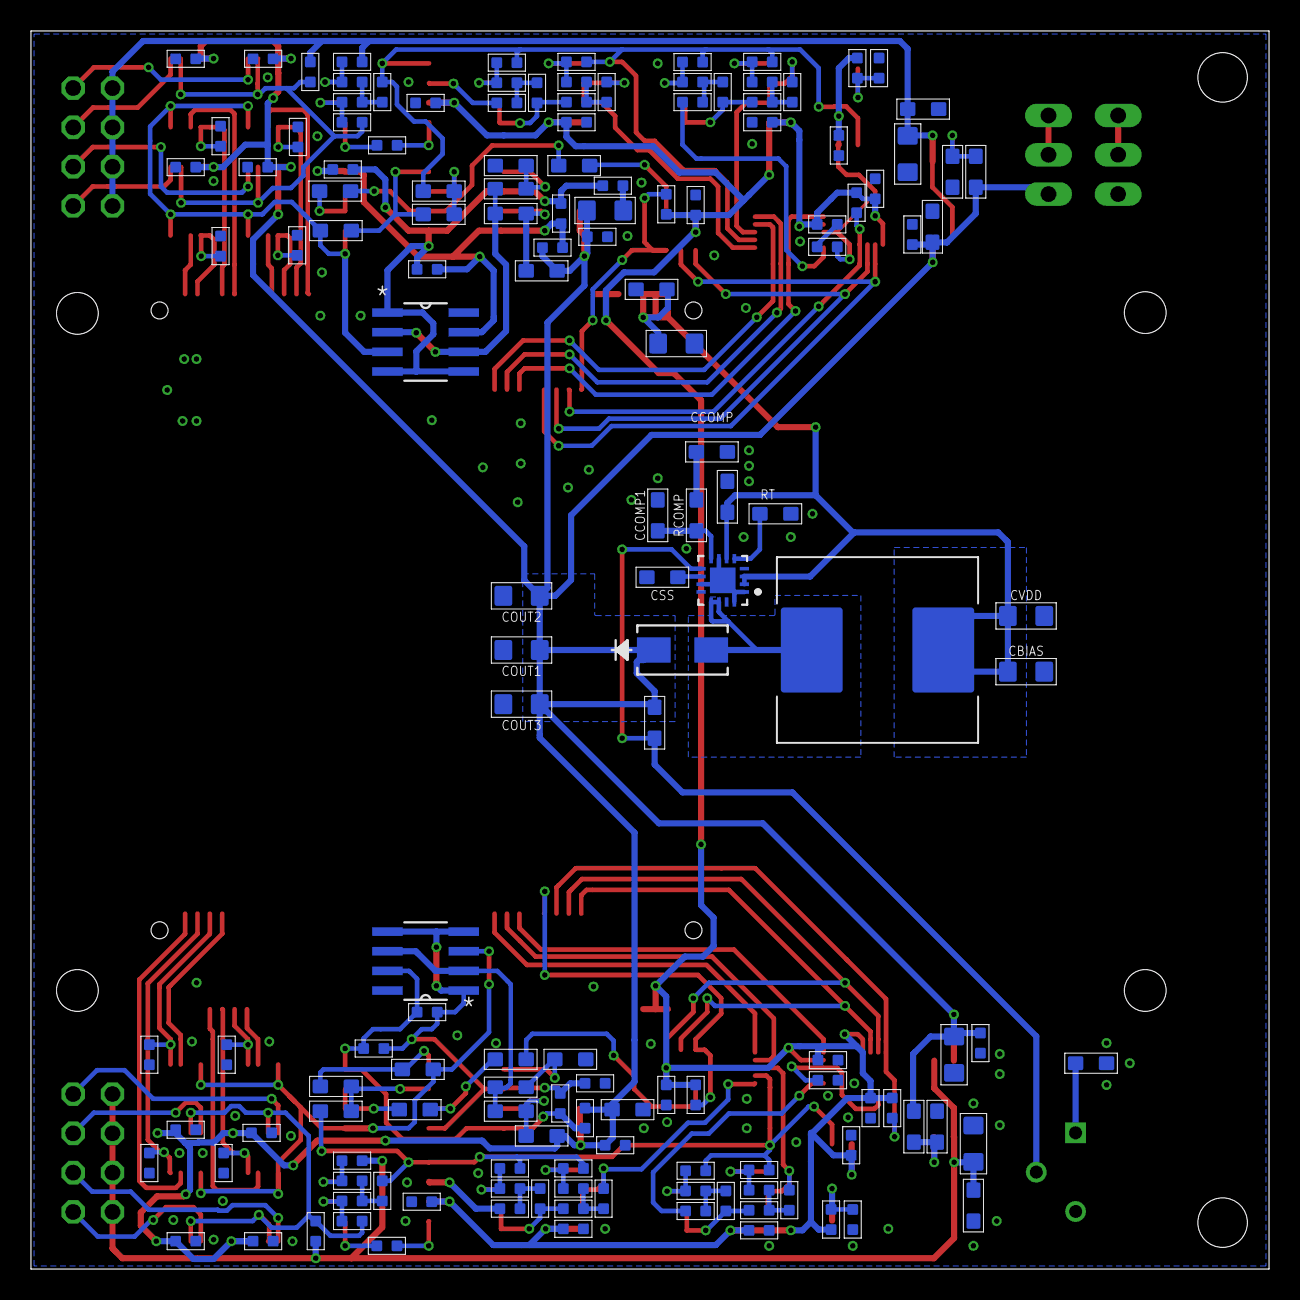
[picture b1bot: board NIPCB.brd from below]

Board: 2 copper layers, 80.0 x 80.0 mm, 184 parts (150 on the bottom side), 123 nets.

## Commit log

2024-09-27 Some scripts
2024-09-27 Added pcb files
2024-09-27 Added xdc files
2024-09-27 Temp file removal
2024-10-22 New files
2024-10-27 Flow works
2024-10-29 More changes to nipcb
2024-10-29 recording files
2024-11-08 hw xil changes
2024-11-08 added some xil sim files
2024-11-08 added working software interface files
2024-11-08 Added READMEs
2024-11-08 added wrong files

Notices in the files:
parts and their libraries:
COPYRIGHT: Copyright (C) 2024 Ultra Librarian. All rights reserved.
